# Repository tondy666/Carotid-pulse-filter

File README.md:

# Carotid-pulse-filter
This is Carotid Pulse Filter 5Hz
this design include board and schematic using eagle software

Copyright ©
Tondy_666

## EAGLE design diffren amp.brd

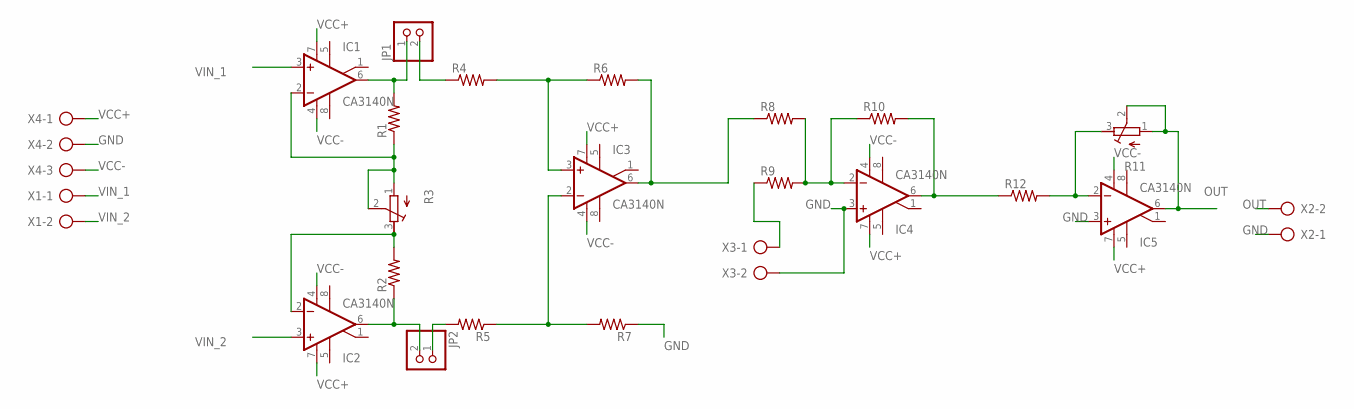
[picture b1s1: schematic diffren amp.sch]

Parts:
IC1, IC2, IC3, IC4, IC5: CA3140N; DIL08
JP1, JP2: PINHD-1X2; 1X02
R1, R2, R4, R5, R6, R7, R8, R9, R10, R12: R-US_0309/12; 0309/12
R3, R11: R-TRIMM64W; RTRIM64W
X1: AK300/2
X2, X3: AK500/2-H
X4: AK300/3

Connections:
GND: IC4.3 (+IN), IC5.3 (+IN), R7.1, X2.1, X3.2, X4.2
unnamed: IC1.6 (OUT), JP1.1, R1.2
unnamed: IC2.6 (OUT), JP2.2, R2.1
unnamed: IC2.2 (-IN), R2.2, R3.3 (E)
unnamed: IC1.2 (-IN), R1.1, R3.1 (A), R3.2 (S)
unnamed: IC3.2 (-IN), R5.1, R7.2
unnamed: IC3.3 (+IN), R4.2, R6.1
unnamed: JP1.2, R4.1
unnamed: JP2.1, R5.2
unnamed: IC4.2 (-IN), R8.2, R9.2, R10.1
unnamed: IC4.6 (OUT), R10.2, R12.1
unnamed: R9.1, X3.1
unnamed: IC5.2 (-IN), R11.3 (E), R12.2
OUT: IC3.6 (OUT), IC5.6 (OUT), R6.2, R8.1, R11.1 (A), R11.2 (S), X2.2
VCC+: IC1.7 (V+), IC2.7 (V+), IC3.7 (V+), IC4.7 (V+), IC5.7 (V+), X4.1
VCC-: IC1.4 (V-), IC2.4 (V-), IC3.4 (V-), IC4.4 (V-), IC5.4 (V-), X4.3
VIN_1: IC1.3 (+IN), X1.1
VIN_2: IC2.3 (+IN), X1.2

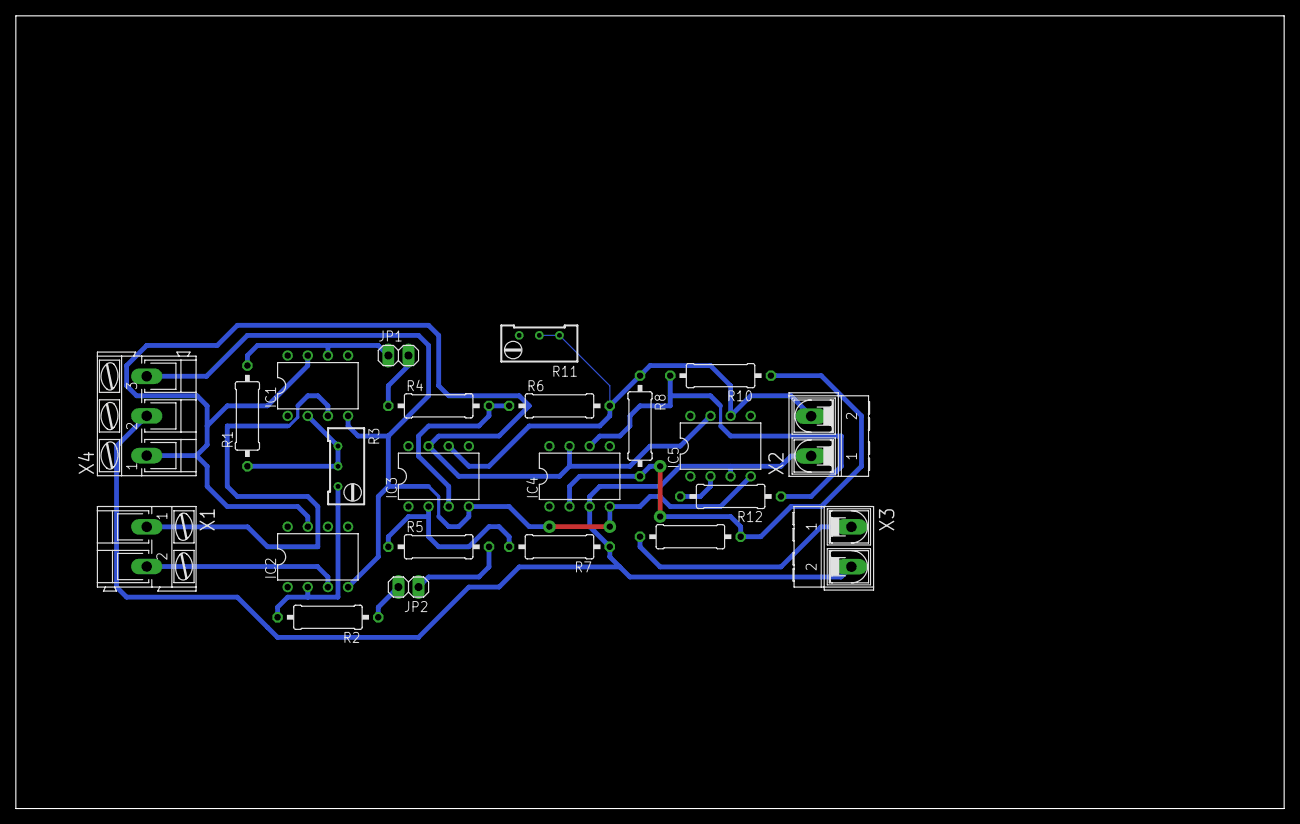
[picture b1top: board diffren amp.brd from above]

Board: 2 copper layers, 160.0 x 100.0 mm, 23 parts (0 on the bottom side), 18 nets.

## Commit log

2020-02-10 Board and Schematic desain with EAGLE
    Carotid pulse filter 5Hz Different AMP + Clamper design circuit with using eagle software
